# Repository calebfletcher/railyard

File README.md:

# railyard
An ecosystem of boards to interface with FPGA boards with PCIe interfaces

| Board  | Description | Location | Status |
| ------ | ----------- | -------- | ------ |
| timemaster | Clock Generator | [boards/timemaster](boards/timemaster/) | Prototype Received |
| hub | Central Interface Hub | [boards/hub](boards/hub/) | In Design |

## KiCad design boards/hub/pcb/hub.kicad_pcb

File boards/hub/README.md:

# Hub

The central interface hub for railyard.

Provides the main PCIe connector to interface with the FPGA, and supplies power to it and to the various other connected boards.

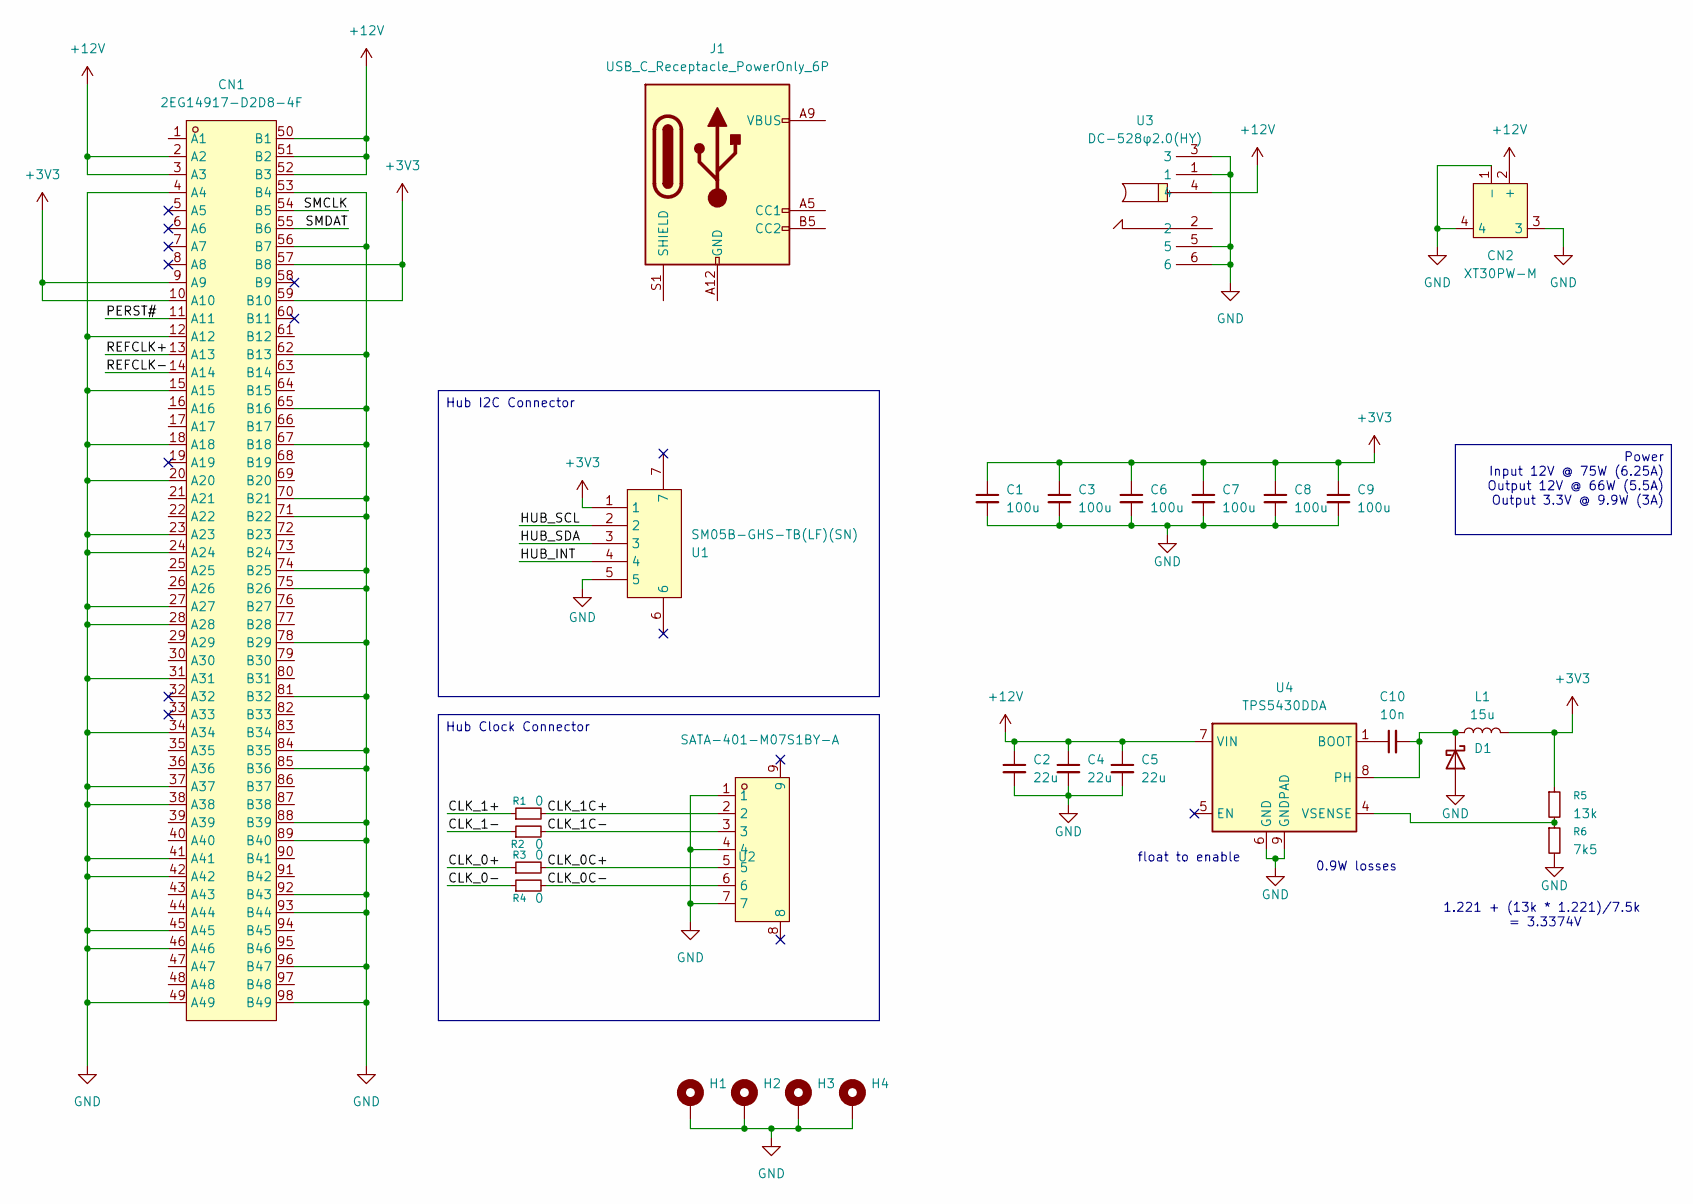
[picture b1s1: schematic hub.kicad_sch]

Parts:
C1, C3, C6, C7, C8, C9: 100u; C_1206_3216Metric; LCSC Part C15008
C2, C4, C5: 22u; C_0805_2012Metric; LCSC Part C45783
C10: 10n; C_0402_1005Metric; LCSC Part C15195
CN1: 2EG14917-D2D8-4F; CONN-TH_2EG14917-D2D8-4F; MPN 2EG14917-D2D8-4F; LCSC Part C426231
CN2: XT30PW-M; CONN-TH_XT30PW-M; LCSC Part C431092
D1: D_Schottky; D_SMA; LCSC Part C22452
H1, H2, H3, H4: MountingHole_Pad; MountingHole_2.2mm_M2_ISO7380_Pad
J1: USB_C_Receptacle_PowerOnly_6P; USB_C_Receptacle_GCT_USB4125-xx-x_6P_TopMnt_Horizontal
L1: 15u; L_Coilcraft_MSS1038-XXX; LCSC Part C18212714
R1, R2, R3, R4: 0; R_0402_1005Metric
R5: 13k; R_0603_1608Metric; LCSC Part C22797
R6: 7k5; R_0603_1608Metric; LCSC Part C23234
U1: SM05B-GHS-TB(LF)(SN); CONN-SMD_5P-P1.25_SM05B-GHS-TB-LF-SN; LCSC Part C189896
U2: SATA-401-M07S1BY-A; CONN-SMD_SATA-401-M07S1BY-A; LCSC Part C7500835
U3: DC-528φ2.0(HY); DC-IN-TH_DC-528-2.0-HY; LCSC Part C2851176
U4: TPS5430DDA; TI_SO-PowerPAD-8_ThermalVias; LCSC Part C9864

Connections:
+3V3: C1.1, C3.1, C6.1, C7.1, C8.1, C9.1, CN1.9 (A9), CN1.10 (A10), CN1.57 (B8), CN1.59 (B10), L1.2, R5.1, U1.1
+12V: C2.1, C4.1, C5.1, CN1.2 (A2), CN1.3 (A3), CN1.50 (B1), CN1.51 (B2), CN1.52 (B3), CN2.2 (+), U3.4, U4.7 (VIN)
/CLK_0+: R3.1
/CLK_0-: R4.1
/CLK_0C+: R3.2, U2.5
/CLK_0C-: R4.2, U2.6
/CLK_1+: R1.1
/CLK_1-: R2.1
/CLK_1C+: R1.2, U2.2
/CLK_1C-: R2.2, U2.3
/HUB_INT: U1.4
/HUB_SCL: U1.2
/HUB_SDA: U1.3
/PERST#: CN1.11 (A11)
/REFCLK+: CN1.13 (A13)
/REFCLK-: CN1.14 (A14)
/SMCLK: CN1.54 (B5)
/SMDAT: CN1.55 (B6)
GND: C1.2, C2.2, C3.2, C4.2, C5.2, C6.2, C7.2, C8.2, C9.2, CN1.4 (A4), CN1.12 (A12), CN1.15 (A15), CN1.18 (A18), CN1.20 (A20), CN1.23 (A23), CN1.24 (A24), CN1.27 (A27), CN1.28 (A28), CN1.31 (A31), CN1.34 (A34), CN1.37 (A37), CN1.38 (A38), CN1.41 (A41), CN1.42 (A42), CN1.45 (A45), CN1.46 (A46), CN1.49 (A49), CN1.53 (B4), CN1.56 (B7), CN1.62 (B13), CN1.65 (B16), CN1.67 (B18), CN1.70 (B21), CN1.71 (B22), CN1.74 (B25), CN1.75 (B26), CN1.78 (B29), CN1.81 (B32), CN1.84 (B35), CN1.85 (B36), CN1.88 (B39), CN1.89 (B40), CN1.92 (B43), CN1.93 (B44), CN1.96 (B47), CN1.98 (B49), CN2.1 (-), CN2.3, CN2.4, D1.2 (A), H1.1, H2.1, H3.1, H4.1, R6.2, U1.5, U2.1, U2.4, U2.7, U3.1, U3.3, U3.5, U3.6, U4.6 (GND), U4.9 (GNDPAD)
unnamed: C10.2, D1.1 (K), L1.1, U4.8 (PH)
unnamed: J1.A12 (GND), J1.B12 (GND)
unnamed: J1.A9 (VBUS), J1.B9 (VBUS)
unnamed: C10.1, U4.1 (BOOT)
unnamed: R5.2, R6.1, U4.4 (VSENSE)

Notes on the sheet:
0.9W losses
float to enable
1.221 + (13k * 1.221)/7.5k = 3.3374V
Power Input 12V @ 75W (6.25A) Output 12V @ 66W (5.5A) Output 3.3V @ 9.9W (3A)
Hub Clock Connector
Hub I2C Connector

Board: 2 copper layers, 27 parts (0 on the bottom side), 12 nets, no tracks yet.

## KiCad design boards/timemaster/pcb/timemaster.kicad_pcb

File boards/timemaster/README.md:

# Timemaster

A Si5340-based clock generator board with two clocks available via a SATA connector, and 2 clocks available via MMCX connectors. All clocks are differential.

Includes a STM32G031G8Ux microcontroller to manage the Si5340, accessible over via I2C on the JST-GH connector.

5 debug LEDs are available to the STM32.

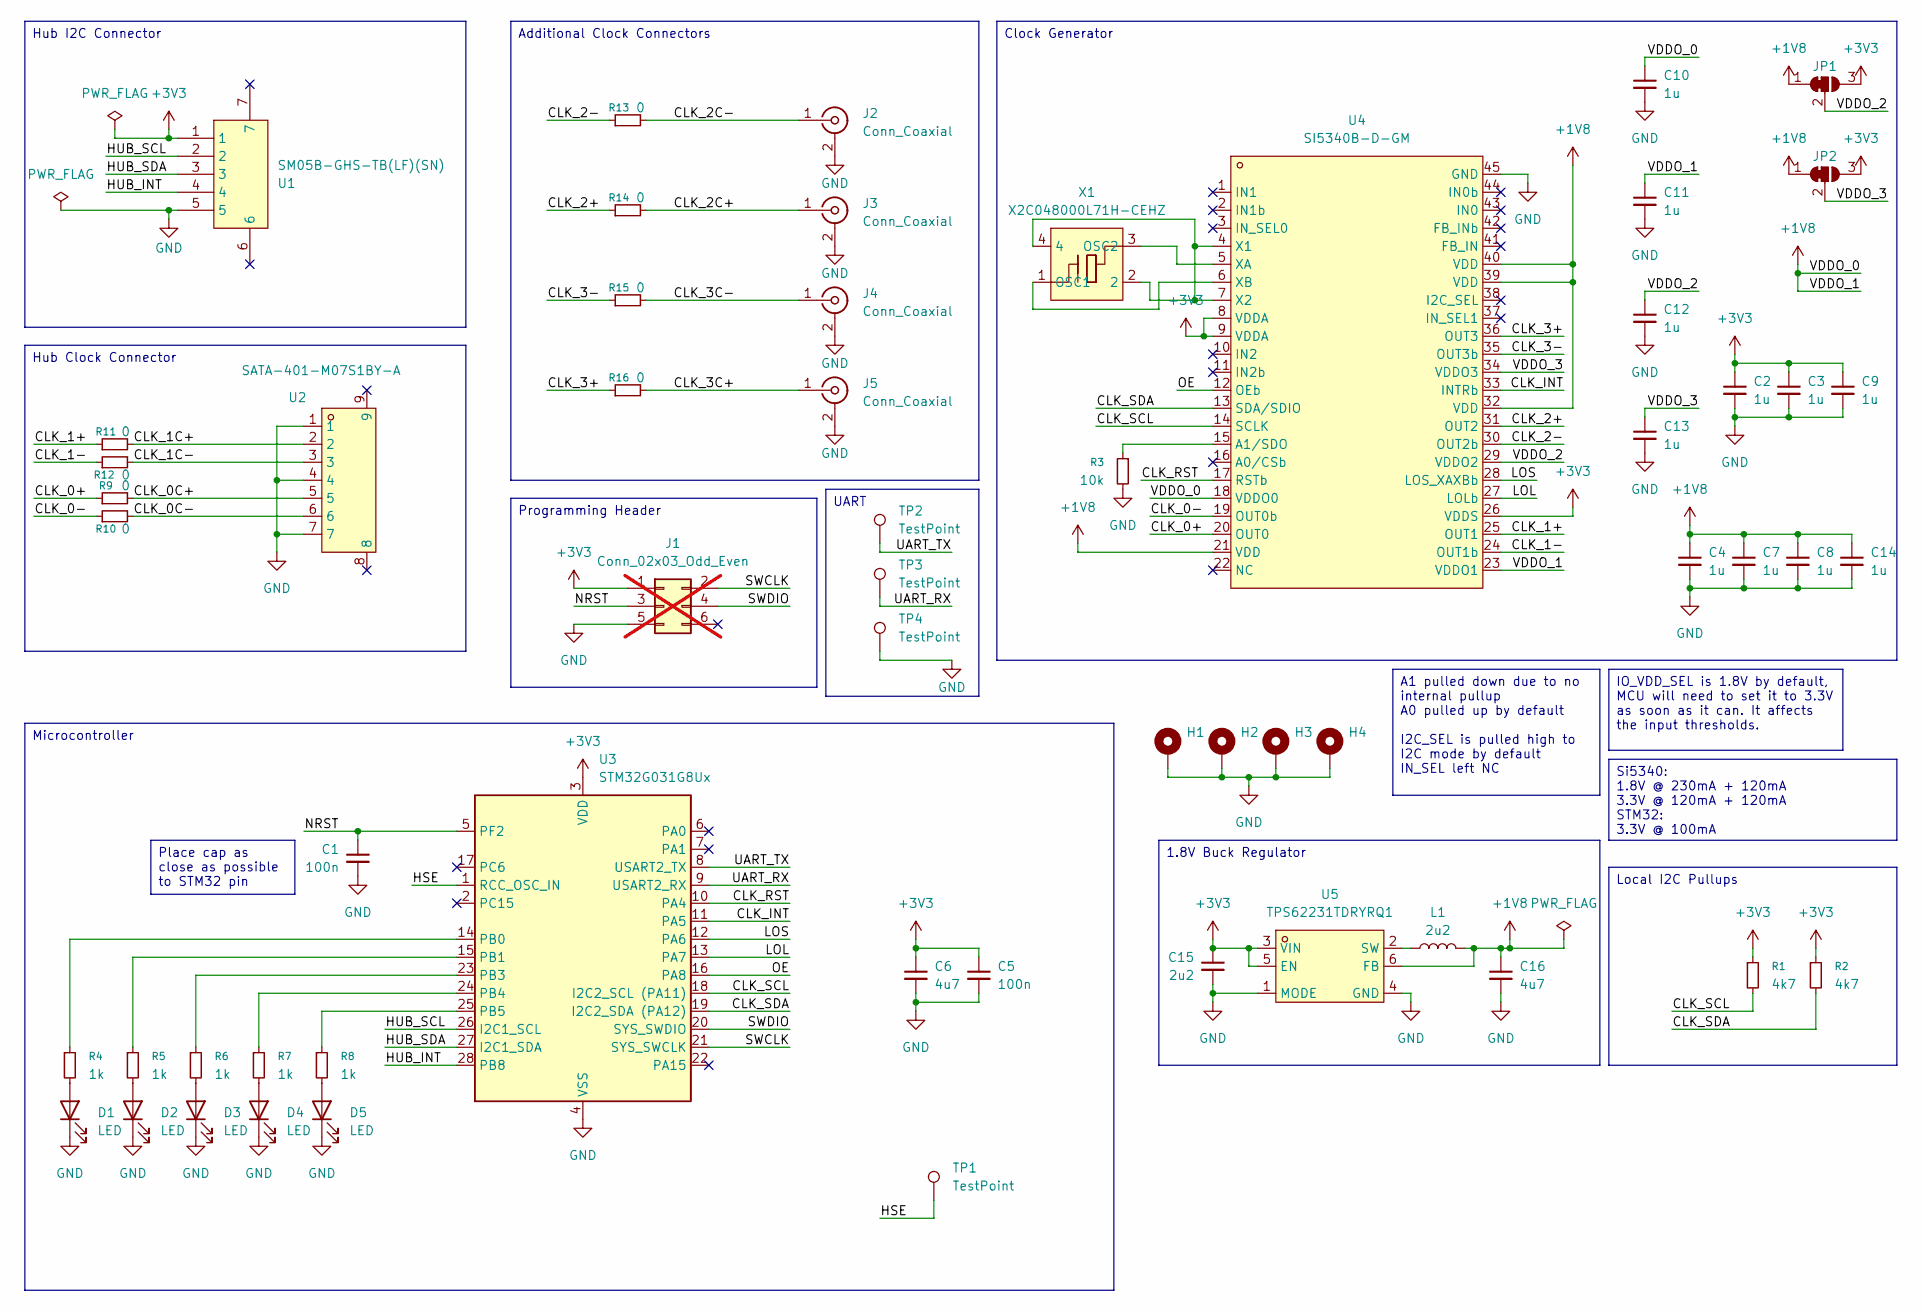
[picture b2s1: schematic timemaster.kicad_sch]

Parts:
C1, C5: 100n; C_0402_1005Metric
C2, C3, C4, C7, C8, C9, C10, C11, C12, C13, C14: 1u; C_0402_1005Metric
C6, C16: 4u7; C_0402_1005Metric
C15: 2u2; C_0402_1005Metric
D1, D2, D3, D4, D5: LED; LED_0805_2012Metric; LCSC Part C2297
H1, H2, H3, H4: MountingHole_Pad; MountingHole_2.2mm_M2_ISO7380_Pad
J1: Conn_02x03_Odd_Even; PinHeader_2x03_P1.27mm_Vertical; not fitted
J2, J3, J4, J5: Conn_Coaxial; MMCX-TH_DL-MMCX-KWE
JP1, JP2: SolderJumper_3_Bridged12; SolderJumper-3_P1.3mm_Bridged12_RoundedPad1.0x1.5mm
L1: 2u2; L_0603_1608Metric; LCSC Part C48888123
R1, R2: 4k7; R_0402_1005Metric
R3: 10k; R_0402_1005Metric
R4, R5, R6, R7, R8: 1k; R_0603_1608Metric
R9, R10, R11, R12, R13, R14, R15, R16: 0; R_0402_1005Metric
TP1, TP2, TP3, TP4: TestPoint; TestPoint_Pad_D1.0mm
U1: SM05B-GHS-TB(LF)(SN); CONN-SMD_5P-P1.25_SM05B-GHS-TB-LF-SN; LCSC Part C189896
U2: SATA-401-M07S1BY-A; CONN-SMD_SATA-401-M07S1BY-A; LCSC Part C7500835
U3: STM32G031G8Ux; QFN-28_4x4mm_P0.5mm; LCSC Part C432211
U4: SI5340B-D-GM; QFN-44_L7.0-W7.0-P0.50-TL-EP5.2; LCSC Part C3607873
U5: TPS62231TDRYRQ1; XSON-6_L1.5-W1.0-P0.50-S0.60-BR; LCSC Part C2070811
X1: X2C048000L71H-CEHZ; CRYSTAL-SMD_4P-L2.0-W1.6-BL; LCSC Part C254326

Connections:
+1V8: C4.1, C7.1, C8.1, C10.1, C11.1, C14.1, C16.1, JP1.1 (A), JP2.1 (A), L1.2, U4.18 (VDDO0), U4.21 (VDD), U4.23 (VDDO1), U4.32 (VDD), U4.39 (VDD), U4.40 (VDD), U5.6 (FB)
+3V3: C2.1, C3.1, C5.1, C6.1, C9.1, C15.1, J1.1, JP1.3 (B), JP2.3 (B), R1.1, R2.1, U1.1, U3.3 (VDD), U4.8 (VDDA), U4.9 (VDDA), U4.26 (VDDS), U5.3 (VIN), U5.5 (EN)
/CLK_0+: R9.1, U4.20 (OUT0)
/CLK_0-: R10.1, U4.19 (OUT0b)
/CLK_0C+: R9.2, U2.5
/CLK_0C-: R10.2, U2.6
/CLK_1+: R11.1, U4.25 (OUT1)
/CLK_1-: R12.1, U4.24 (OUT1b)
/CLK_1C+: R11.2, U2.2
/CLK_1C-: R12.2, U2.3
/CLK_2+: R14.1, U4.31 (OUT2)
/CLK_2-: R13.1, U4.30 (OUT2b)
/CLK_2C+: J3.1 (In), R14.2
/CLK_2C-: J2.1 (In), R13.2
/CLK_3+: R16.1, U4.36 (OUT3)
/CLK_3-: R15.1, U4.35 (OUT3b)
/CLK_3C+: J5.1 (In), R16.2
/CLK_3C-: J4.1 (In), R15.2
/CLK_INT: U3.11 (PA5), U4.33 (INTRb)
/CLK_RST: U3.10 (PA4), U4.17 (RSTb)
/CLK_SCL: R1.2, U3.18 (I2C2_SCL (PA11)), U4.14 (SCLK)
/CLK_SDA: R2.2, U3.19 (I2C2_SDA (PA12)), U4.13 (SDA/SDIO)
/HSE: TP1.1, U3.1 (RCC_OSC_IN)
/HUB_INT: U1.4, U3.28 (PB8)
/HUB_SCL: U1.2, U3.26 (I2C1_SCL)
/HUB_SDA: U1.3, U3.27 (I2C1_SDA)
/LOL: U3.13 (PA7), U4.27 (LOLb)
/LOS: U3.12 (PA6), U4.28 (LOS_XAXBb)
/NRST: C1.1, J1.3, U3.5 (PF2)
/OE: U3.16 (PA8), U4.12 (OEb)
/SWCLK: J1.2, U3.21 (SYS_SWCLK)
/SWDIO: J1.4, U3.20 (SYS_SWDIO)
/UART_RX: TP3.1, U3.9 (USART2_RX)
/UART_TX: TP2.1, U3.8 (USART2_TX)
/VDDO_2: C12.1, JP1.2 (C), U4.29 (VDDO2)
/VDDO_3: C13.1, JP2.2 (C), U4.34 (VDDO3)
GND: C1.2, C2.2, C3.2, C4.2, C5.2, C6.2, C7.2, C8.2, C9.2, C10.2, C11.2, C12.2, C13.2, C14.2, C15.2, C16.2, D1.1 (K), D2.1 (K), D3.1 (K), D4.1 (K), D5.1 (K), H1.1, H2.1, H3.1, H4.1, J1.5, J2.2 (Ext), J3.2 (Ext), J4.2 (Ext), J5.2 (Ext), R3.2, TP4.1, U1.5, U2.1, U2.4, U2.7, U3.4 (VSS), U4.45 (GND), U5.1 (MODE), U5.4 (GND)
unnamed: D1.2 (A), R4.2
unnamed: D2.2 (A), R5.2
unnamed: D3.2 (A), R6.2
unnamed: D4.2 (A), R7.2
unnamed: D5.2 (A), R8.2
unnamed: R4.1, U3.14 (PB0)
unnamed: R5.1, U3.15 (PB1)
unnamed: R6.1, U3.23 (PB3)
unnamed: R7.1, U3.24 (PB4)
unnamed: R8.1, U3.25 (PB5)
unnamed: R3.1, U4.15 (A1/SDO)
unnamed: U4.4 (X1), U4.7 (X2), X1.2, X1.4
unnamed: U4.5 (XA), X1.3 (OSC2)
unnamed: U4.6 (XB), X1.1 (OSC1)
unnamed: L1.1, U5.2 (SW)

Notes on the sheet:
Local I2C Pullups
Hub I2C Connector
UART
Programming Header
Place cap as close as possible to STM32 pin
A1 pulled down due to no internal pullup A0 pulled up by default I2C_SEL is pulled high to I2C mode by default IN_SEL left NC
Hub Clock Connector
Si5340: 1.8V @ 230mA + 120mA 3.3V @ 120mA + 120mA STM32: 3.3V @ 100mA
IO_VDD_SEL is 1.8V by default, MCU will need to set it to 3.3V as soon as it can. It affects the input thresholds.
Microcontroller
1.8V Buck Regulator
Clock Generator
Additional Clock Connectors

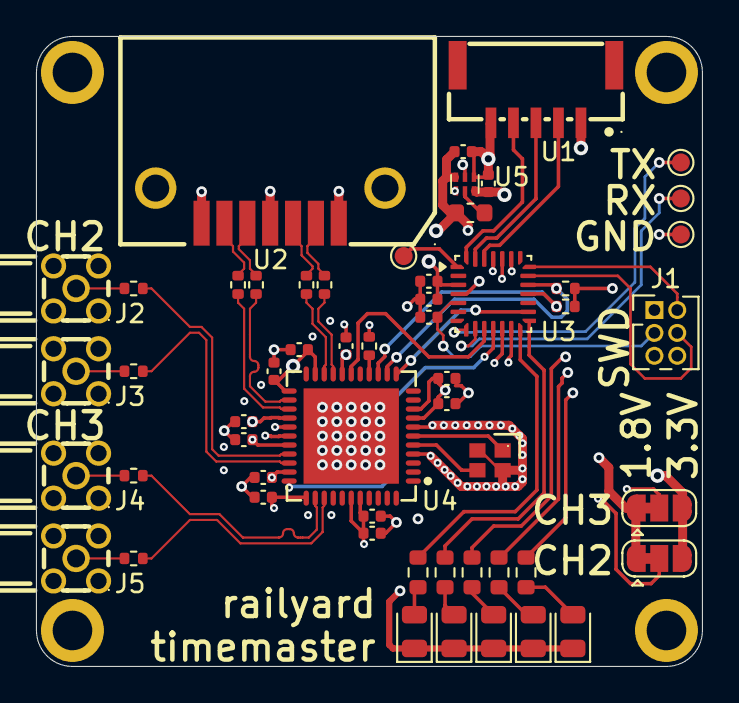
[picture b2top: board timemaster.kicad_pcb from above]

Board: 6 copper layers, 37.0 x 35.0 mm, 59 parts (0 on the bottom side), 52 nets.

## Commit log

2026-03-10 timemaster: initial commit
2026-03-10 update project name to railyard
2026-03-10 timemaster: rev b with larger vias for jlc
2026-03-10 timemaster: set drc for jlc via sizes
2026-03-10 timemaster: add readme
2026-03-23 timemaster: add photo of received unit
2026-03-24 hub: add readme
2026-03-24 timemaster: add firmware crate with rtic structure
2026-03-24 timemaster: first blinky on hardware
2026-03-24 hub: initial schematic planning
2026-03-24 hub: fix link
2026-03-24 timemaster: clean up firmware build
2026-03-24 timemaster: bump clock rate to 64MHz
2026-03-24 timemaster: read id from si5340
2026-03-24 timemaster: add si5340 crate
